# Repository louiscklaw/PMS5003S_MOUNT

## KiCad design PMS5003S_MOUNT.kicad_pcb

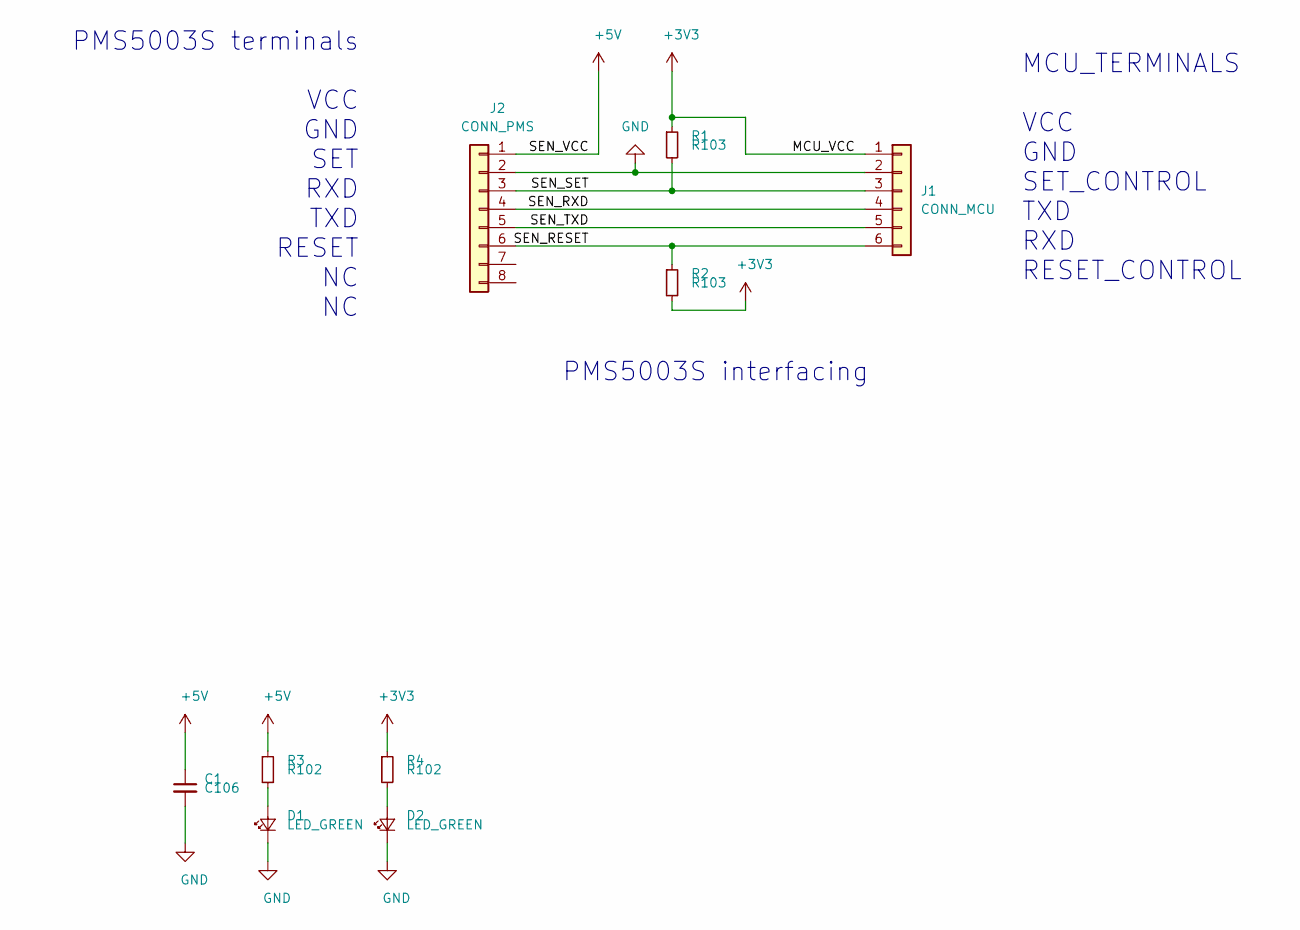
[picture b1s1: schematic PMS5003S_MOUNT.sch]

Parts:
C1: C106; C_0805_2012Metric_Pad1.15x1.40mm_HandSolder
D1, D2: LED_GREEN; LED_0805_2012Metric_Pad1.15x1.40mm_HandSolder
J1: CONN_MCU; PinHeader_1x06_P2.54mm_Vertical
J2: CONN_PMS; PMS5003S
R1, R2: R103; R_0805_2012Metric_Pad1.15x1.40mm_HandSolder
R3, R4: R102; R_0805_2012Metric_Pad1.15x1.40mm_HandSolder

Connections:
+3V3: J1.1, R1.1, R2.2, R4.1
+5V: C1.1, J2.1, R3.1
/SEN_RESET: J1.6, J2.6, R2.1
/SEN_RXD: J1.4, J2.4
/SEN_SET: J1.3, J2.3, R1.2
/SEN_TXD: J1.5, J2.5
GND: C1.2, D1.1 (K), D2.1 (K), J1.2, J2.2
unnamed: D1.2 (A), R3.2
unnamed: D2.2 (A), R4.2

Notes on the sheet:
PMS5003S interfacing
PMS5003S terminals VCC GND SET RXD TXD RESET NC NC
MCU_TERMINALS VCC GND SET_CONTROL TXD RXD RESET_CONTROL

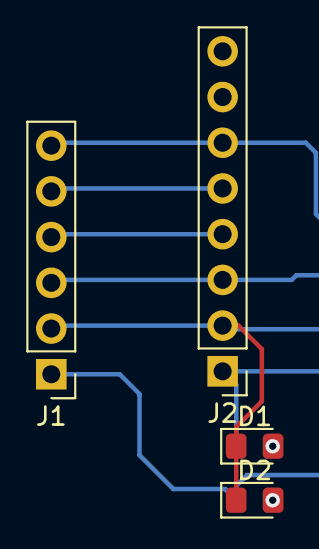
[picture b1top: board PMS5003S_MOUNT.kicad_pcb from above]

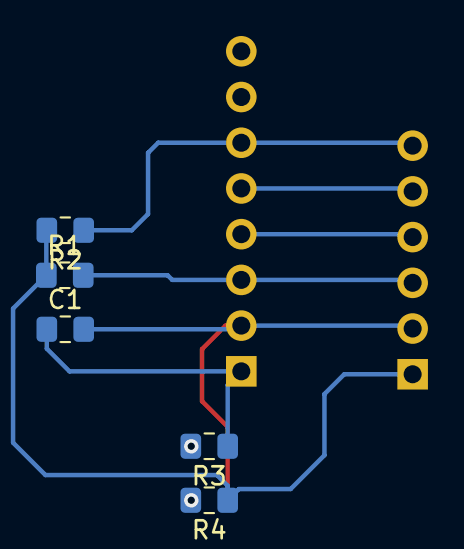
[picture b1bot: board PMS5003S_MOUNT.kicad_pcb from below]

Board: 2 copper layers, 9 parts (5 on the bottom side), 9 nets.

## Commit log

2018-10-10 init update,
2018-10-15 updte
2018-10-16 update,
